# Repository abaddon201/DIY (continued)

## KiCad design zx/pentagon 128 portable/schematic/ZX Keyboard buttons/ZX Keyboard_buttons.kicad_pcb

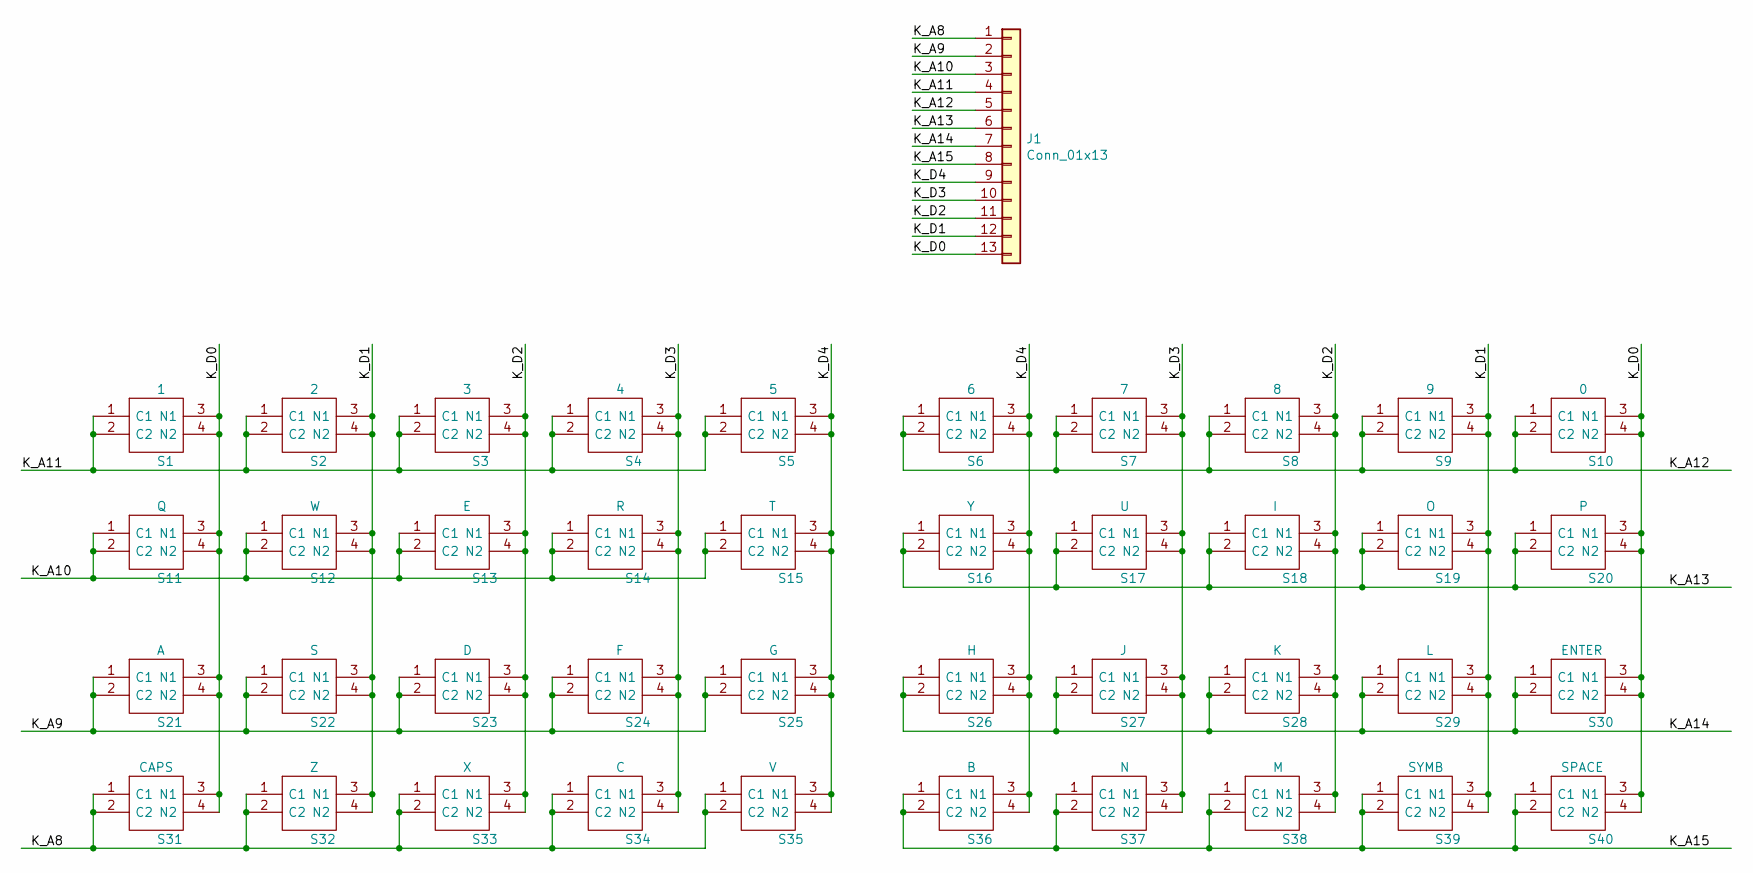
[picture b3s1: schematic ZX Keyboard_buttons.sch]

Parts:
J1: Conn_01x13; PinHeader_1x13_P2.54mm_Vertical
S1: 1; 118259104; Mouser Part Number 506-1-1825910-4
S2: 2; 118259104; Mouser Part Number 506-1-1825910-4
S3: 3; 118259104; Mouser Part Number 506-1-1825910-4
S4: 4; 118259104; Mouser Part Number 506-1-1825910-4
S5: 5; 118259104; Mouser Part Number 506-1-1825910-4
S6: 6; 118259104; Mouser Part Number 506-1-1825910-4
S7: 7; 118259104; Mouser Part Number 506-1-1825910-4
S8: 8; 118259104; Mouser Part Number 506-1-1825910-4
S9: 9; 118259104; Mouser Part Number 506-1-1825910-4
S10: 0; 118259104; Mouser Part Number 506-1-1825910-4
S11: Q; 118259104; Mouser Part Number 506-1-1825910-4
S12: W; 118259104; Mouser Part Number 506-1-1825910-4
S13: E; 118259104; Mouser Part Number 506-1-1825910-4
S14: R; 118259104; Mouser Part Number 506-1-1825910-4
S15: T; 118259104; Mouser Part Number 506-1-1825910-4
S16: Y; 118259104; Mouser Part Number 506-1-1825910-4
S17: U; 118259104; Mouser Part Number 506-1-1825910-4
S18: I; 118259104; Mouser Part Number 506-1-1825910-4
S19: O; 118259104; Mouser Part Number 506-1-1825910-4
S20: P; 118259104; Mouser Part Number 506-1-1825910-4
S21: A; 118259104; Mouser Part Number 506-1-1825910-4
S22: S; 118259104; Mouser Part Number 506-1-1825910-4
S23: D; 118259104; Mouser Part Number 506-1-1825910-4
S24: F; 118259104; Mouser Part Number 506-1-1825910-4
S25: G; 118259104; Mouser Part Number 506-1-1825910-4
S26: H; 118259104; Mouser Part Number 506-1-1825910-4
S27: J; 118259104; Mouser Part Number 506-1-1825910-4
S28: K; 118259104; Mouser Part Number 506-1-1825910-4
S29: L; 118259104; Mouser Part Number 506-1-1825910-4
S30: ENTER; 118259104; Mouser Part Number 506-1-1825910-4
S31: CAPS; 118259104; Mouser Part Number 506-1-1825910-4
S32: Z; 118259104; Mouser Part Number 506-1-1825910-4
S33: X; 118259104; Mouser Part Number 506-1-1825910-4
S34: C; 118259104; Mouser Part Number 506-1-1825910-4
S35: V; 118259104; Mouser Part Number 506-1-1825910-4
S36: B; 118259104; Mouser Part Number 506-1-1825910-4
S37: N; 118259104; Mouser Part Number 506-1-1825910-4
S38: M; 118259104; Mouser Part Number 506-1-1825910-4
S39: SYMB; 118259104; Mouser Part Number 506-1-1825910-4
S40: SPACE; 118259104; Mouser Part Number 506-1-1825910-4

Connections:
/K_A8: J1.1, S31.1 (C1), S31.2 (C2), S32.1 (C1), S32.2 (C2), S33.1 (C1), S33.2 (C2), S34.1 (C1), S34.2 (C2), S35.1 (C1), S35.2 (C2)
/K_A9: J1.2, S21.1 (C1), S21.2 (C2), S22.1 (C1), S22.2 (C2), S23.1 (C1), S23.2 (C2), S24.1 (C1), S24.2 (C2), S25.1 (C1), S25.2 (C2)
/K_A10: J1.3, S11.1 (C1), S11.2 (C2), S12.1 (C1), S12.2 (C2), S13.1 (C1), S13.2 (C2), S14.1 (C1), S14.2 (C2), S15.1 (C1), S15.2 (C2)
/K_A11: J1.4, S1.1 (C1), S1.2 (C2), S2.1 (C1), S2.2 (C2), S3.1 (C1), S3.2 (C2), S4.1 (C1), S4.2 (C2), S5.1 (C1), S5.2 (C2)
/K_A12: J1.5, S6.1 (C1), S6.2 (C2), S7.1 (C1), S7.2 (C2), S8.1 (C1), S8.2 (C2), S9.1 (C1), S9.2 (C2), S10.1 (C1), S10.2 (C2)
/K_A13: J1.6, S16.1 (C1), S16.2 (C2), S17.1 (C1), S17.2 (C2), S18.1 (C1), S18.2 (C2), S19.1 (C1), S19.2 (C2), S20.1 (C1), S20.2 (C2)
/K_A14: J1.7, S26.1 (C1), S26.2 (C2), S27.1 (C1), S27.2 (C2), S28.1 (C1), S28.2 (C2), S29.1 (C1), S29.2 (C2), S30.1 (C1), S30.2 (C2)
/K_A15: J1.8, S36.1 (C1), S36.2 (C2), S37.1 (C1), S37.2 (C2), S38.1 (C1), S38.2 (C2), S39.1 (C1), S39.2 (C2), S40.1 (C1), S40.2 (C2)
/K_D0: J1.13, S1.3 (N1), S1.4 (N2), S10.3 (N1), S10.4 (N2), S11.3 (N1), S11.4 (N2), S20.3 (N1), S20.4 (N2), S21.3 (N1), S21.4 (N2), S30.3 (N1), S30.4 (N2), S31.3 (N1), S31.4 (N2), S40.3 (N1), S40.4 (N2)
/K_D1: J1.12, S2.3 (N1), S2.4 (N2), S9.3 (N1), S9.4 (N2), S12.3 (N1), S12.4 (N2), S19.3 (N1), S19.4 (N2), S22.3 (N1), S22.4 (N2), S29.3 (N1), S29.4 (N2), S32.3 (N1), S32.4 (N2), S39.3 (N1), S39.4 (N2)
/K_D2: J1.11, S3.3 (N1), S3.4 (N2), S8.3 (N1), S8.4 (N2), S13.3 (N1), S13.4 (N2), S18.3 (N1), S18.4 (N2), S23.3 (N1), S23.4 (N2), S28.3 (N1), S28.4 (N2), S33.3 (N1), S33.4 (N2), S38.3 (N1), S38.4 (N2)
/K_D3: J1.10, S4.3 (N1), S4.4 (N2), S7.3 (N1), S7.4 (N2), S14.3 (N1), S14.4 (N2), S17.3 (N1), S17.4 (N2), S24.3 (N1), S24.4 (N2), S27.3 (N1), S27.4 (N2), S34.3 (N1), S34.4 (N2), S37.3 (N1), S37.4 (N2)
/K_D4: J1.9, S5.3 (N1), S5.4 (N2), S6.3 (N1), S6.4 (N2), S15.3 (N1), S15.4 (N2), S16.3 (N1), S16.4 (N2), S25.3 (N1), S25.4 (N2), S26.3 (N1), S26.4 (N2), S35.3 (N1), S35.4 (N2), S36.3 (N1), S36.4 (N2)

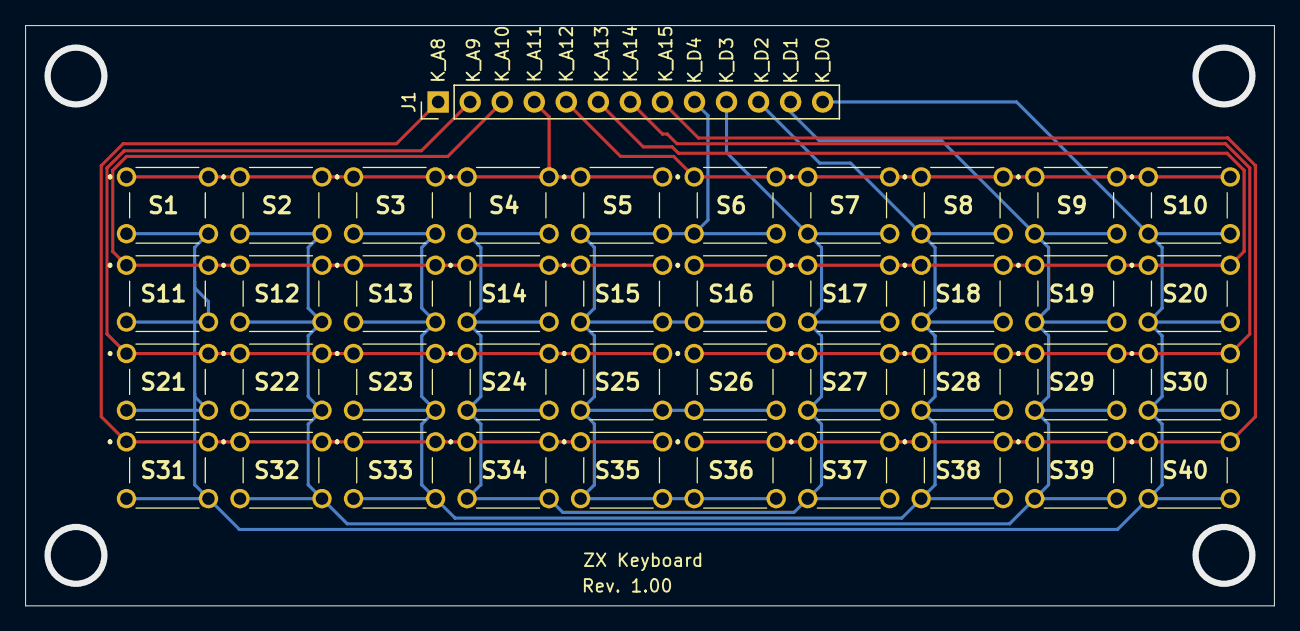
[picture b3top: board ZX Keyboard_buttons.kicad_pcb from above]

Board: 2 copper layers, 99.0 x 46.0 mm, 41 parts (0 on the bottom side), 13 nets.

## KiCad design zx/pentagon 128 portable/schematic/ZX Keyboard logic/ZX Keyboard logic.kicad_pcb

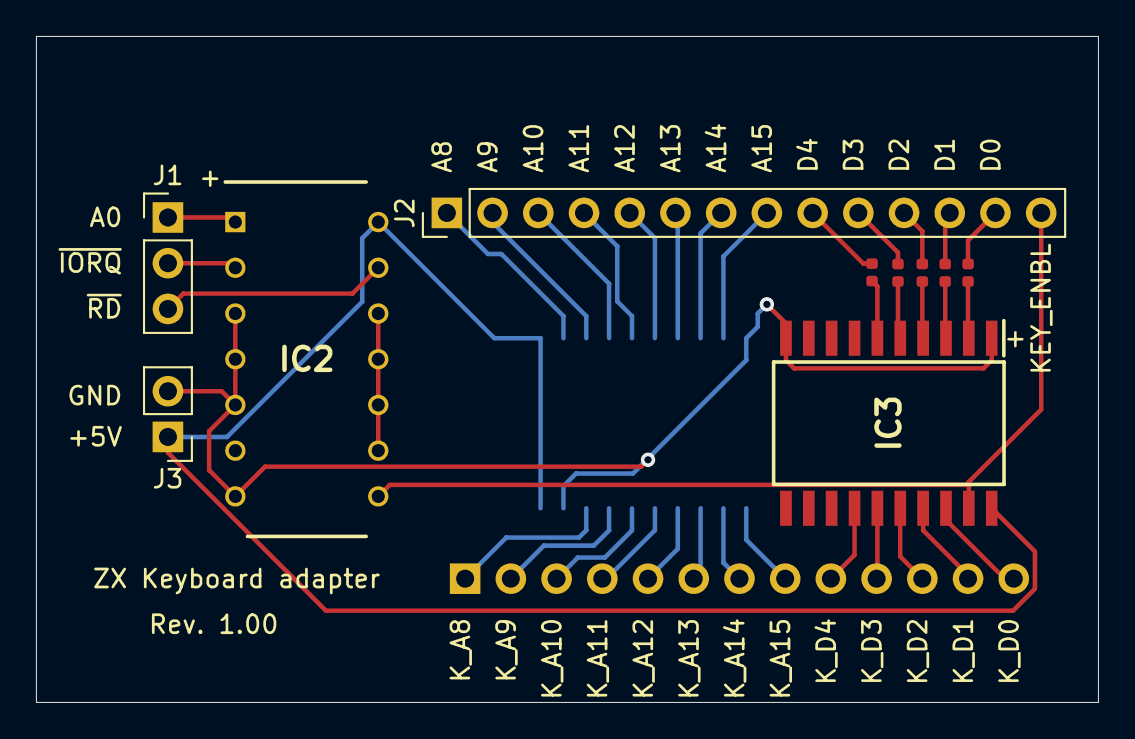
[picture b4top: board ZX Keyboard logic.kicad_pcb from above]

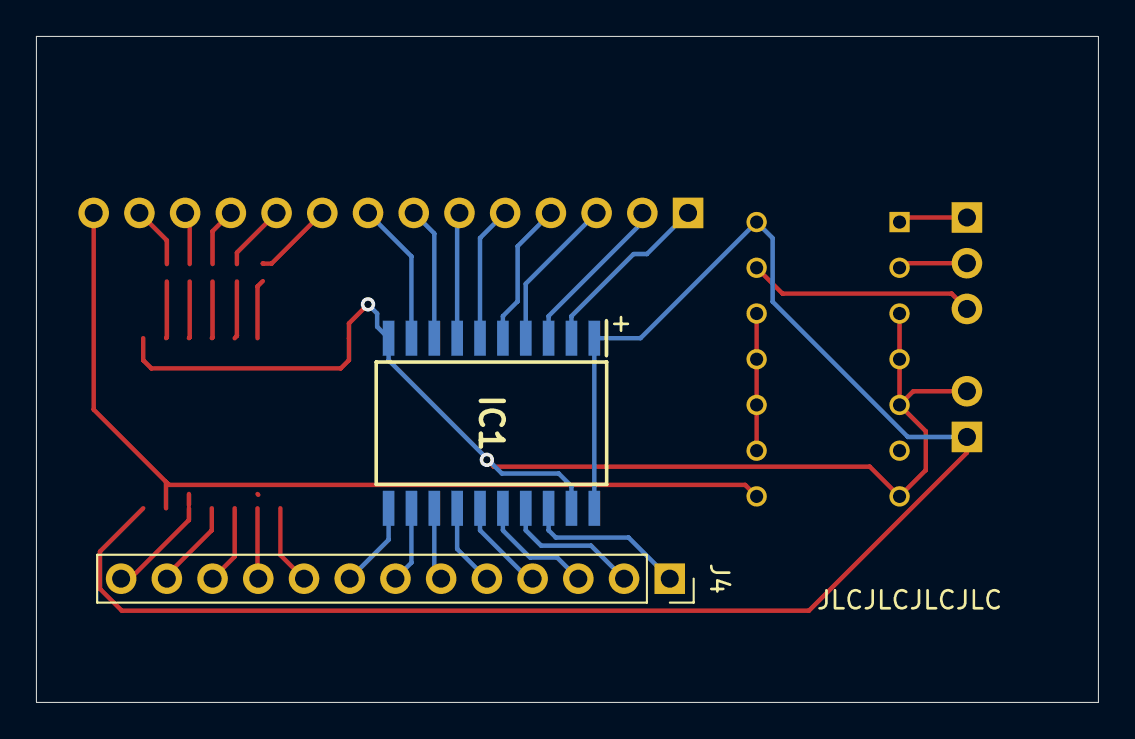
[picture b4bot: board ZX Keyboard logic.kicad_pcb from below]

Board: 2 copper layers, 59.0 x 37.0 mm, 12 parts (2 on the bottom side), 38 nets.

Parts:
IC1, IC3: SN74LS245DW; SOIC127P1030X265-20N
IC2: SN74LS27N; DIP794W53P254L1930H508Q14N
J1: Conn_01x03; PinHeader_1x03_P2.54mm_Vertical
J2: Conn_01x14; PinHeader_1x14_P2.54mm_Vertical
J3: Conn_01x02; PinHeader_1x02_P2.54mm_Vertical
J4: Conn_01x13; PinSocket_1x13_P2.54mm_Vertical
R1, R2, R3, R4: 1.5K; R_0402_1005Metric
R?-R1: 1.5K; R_0402_1005Metric

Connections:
+5V: IC1.1, IC1.20, IC2.14, IC3.20, J3.1
/A0: IC2.1, J1.1
/A8: IC1.2, J2.1
/A9: IC1.3, J2.2
/A10: IC1.4, J2.3
/A11: IC1.5, J2.4
/A12: IC1.6, J2.5
/A13: IC1.7, J2.6
/A14: IC1.8, J2.7
/A15: IC1.9, J2.8
/D0: J2.13, R?-R1.2
/D1: J2.12, R1.2
/D2: J2.11, R2.2
/D3: J2.10, R3.2
/D4: J2.9, R4.2
/KEY_ENBL: IC2.8, IC3.19, J2.14
/K_A8: IC1.18, J4.1
/K_A9: IC1.17, J4.2
/K_A10: IC1.16, J4.3
/K_A11: IC1.15, J4.4
/K_A12: IC1.14, J4.5
/K_A13: IC1.13, J4.6
/K_A14: IC1.12, J4.7
/K_A15: IC1.11, J4.8
/K_D0: IC3.18, J4.13
/K_D1: IC3.17, J4.12
/K_D2: IC3.16, J4.11
/K_D3: IC3.15, J4.10
/K_D4: IC3.14, J4.9
/~IORQ: IC2.2, J1.2
/~RD: IC2.13, J1.3
GND: IC1.10, IC1.19, IC2.3, IC2.4, IC2.5, IC2.7, IC3.1, IC3.10, J3.2
unnamed: IC2.9, IC2.10, IC2.11, IC2.12
unnamed: IC3.2, R?-R1.1
unnamed: IC3.3, R1.1
unnamed: IC3.4, R2.1
unnamed: IC3.5, R3.1
unnamed: IC3.6, R4.1

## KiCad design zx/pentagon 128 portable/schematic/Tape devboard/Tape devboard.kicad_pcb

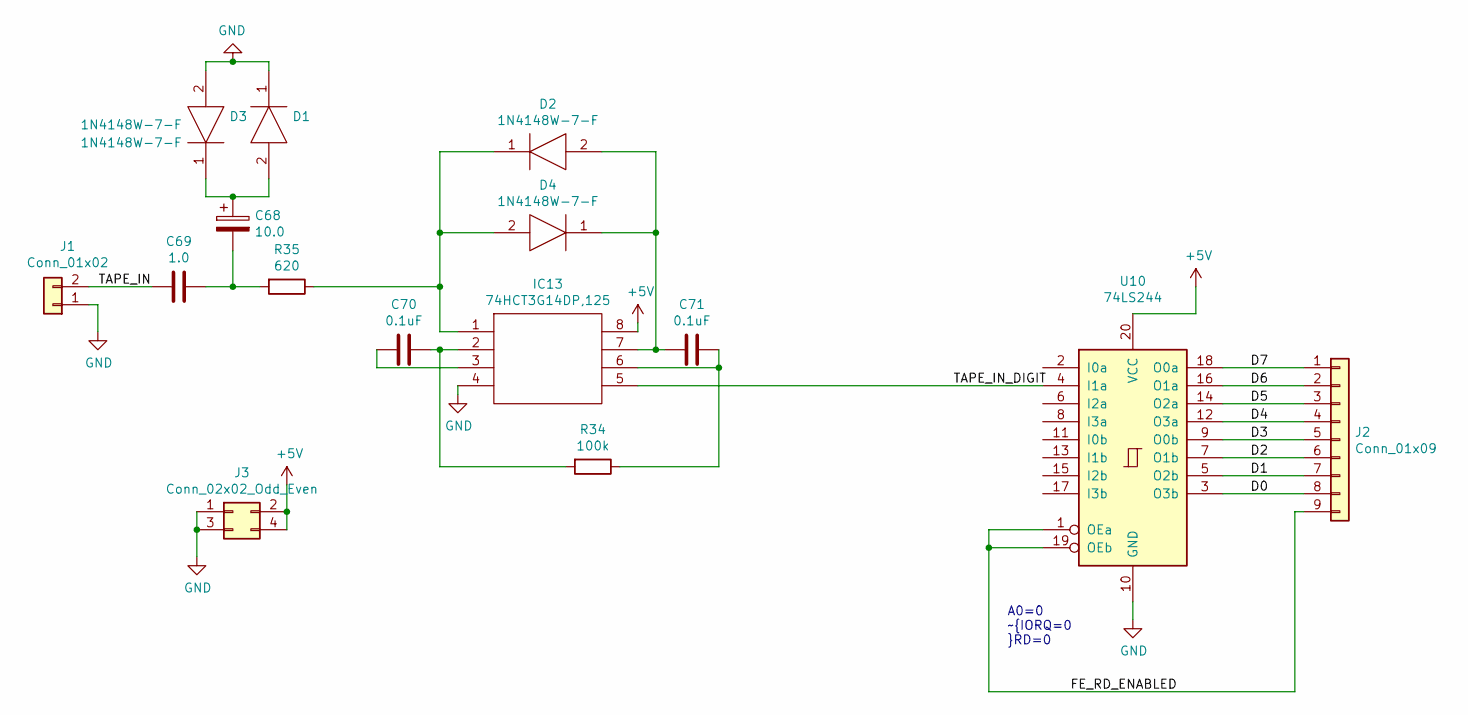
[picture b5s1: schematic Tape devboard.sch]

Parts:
C68: 10.0; C_0402_1005Metric
C69: 1.0; C_0402_1005Metric
C70, C71: 0.1uF; C_0402_1005Metric
D1, D2, D3, D4: 1N4148W-7-F; SOD3716X145N; Mouser Part Number 621-1N4148W-F
IC13: 74HCT3G14DP,125; SOP65P400X110-8N; Mouser Part Number 771-HCT3G14DP125
J1: Conn_01x02; PinHeader_1x02_P2.54mm_Vertical
J2: Conn_01x09; PinHeader_1x09_P2.54mm_Vertical
J3: Conn_02x02_Odd_Even; PinHeader_2x02_P2.54mm_Vertical
R34: 100k; R_0402_1005Metric
R35: 620; R_0402_1005Metric
U10: 74LS244; SSOP-20_5.3x7.2mm_P0.65mm; Mouser Part Number 595-SN74LS244DBR

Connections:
+5V: IC13.8, J3.2, J3.4, U10.20 (VCC)
/D0: J2.8, U10.3 (O3b)
/D1: J2.7, U10.5 (O2b)
/D2: J2.6, U10.7 (O1b)
/D3: J2.5, U10.9 (O0b)
/D4: J2.4, U10.12 (O3a)
/D5: J2.3, U10.14 (O2a)
/D6: J2.2, U10.16 (O1a)
/D7: J2.1, U10.18 (O0a)
/FE_RD_ENABLED: J2.9, U10.1 (OEa), U10.19 (OEb)
/TAPE_IN: C69.2, J1.2
/TAPE_IN_DIGIT: IC13.5, U10.4 (I1a)
GND: D1.1, D3.2, IC13.4, J1.1, J3.1, J3.3, U10.10 (GND)
unnamed: C68.1, D1.2, D3.1
unnamed: C68.2, C69.1, R35.2
unnamed: C70.1, IC13.2, R34.2
unnamed: C70.2, IC13.3
unnamed: C71.1, IC13.6, R34.1
unnamed: C71.2, D2.2, D4.1, IC13.7
unnamed: D2.1, D4.2, IC13.1, R35.1

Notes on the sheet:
A0=0 ~IORQ=0 ~RD=0

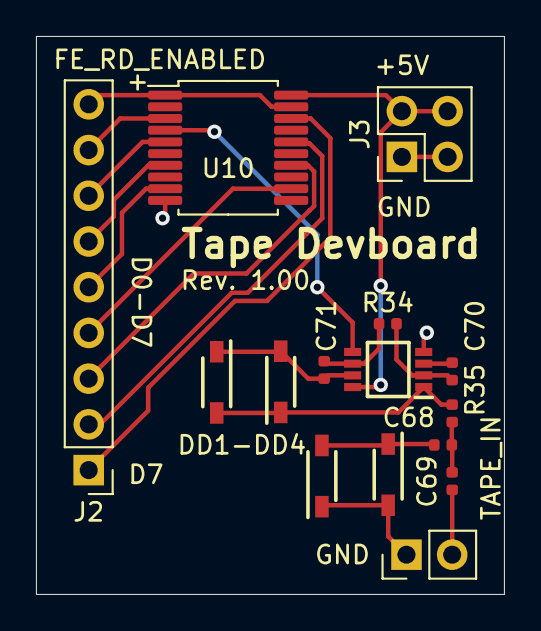
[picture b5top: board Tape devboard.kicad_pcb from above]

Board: 2 copper layers, 26.0 x 31.0 mm, 15 parts (0 on the bottom side), 20 nets.

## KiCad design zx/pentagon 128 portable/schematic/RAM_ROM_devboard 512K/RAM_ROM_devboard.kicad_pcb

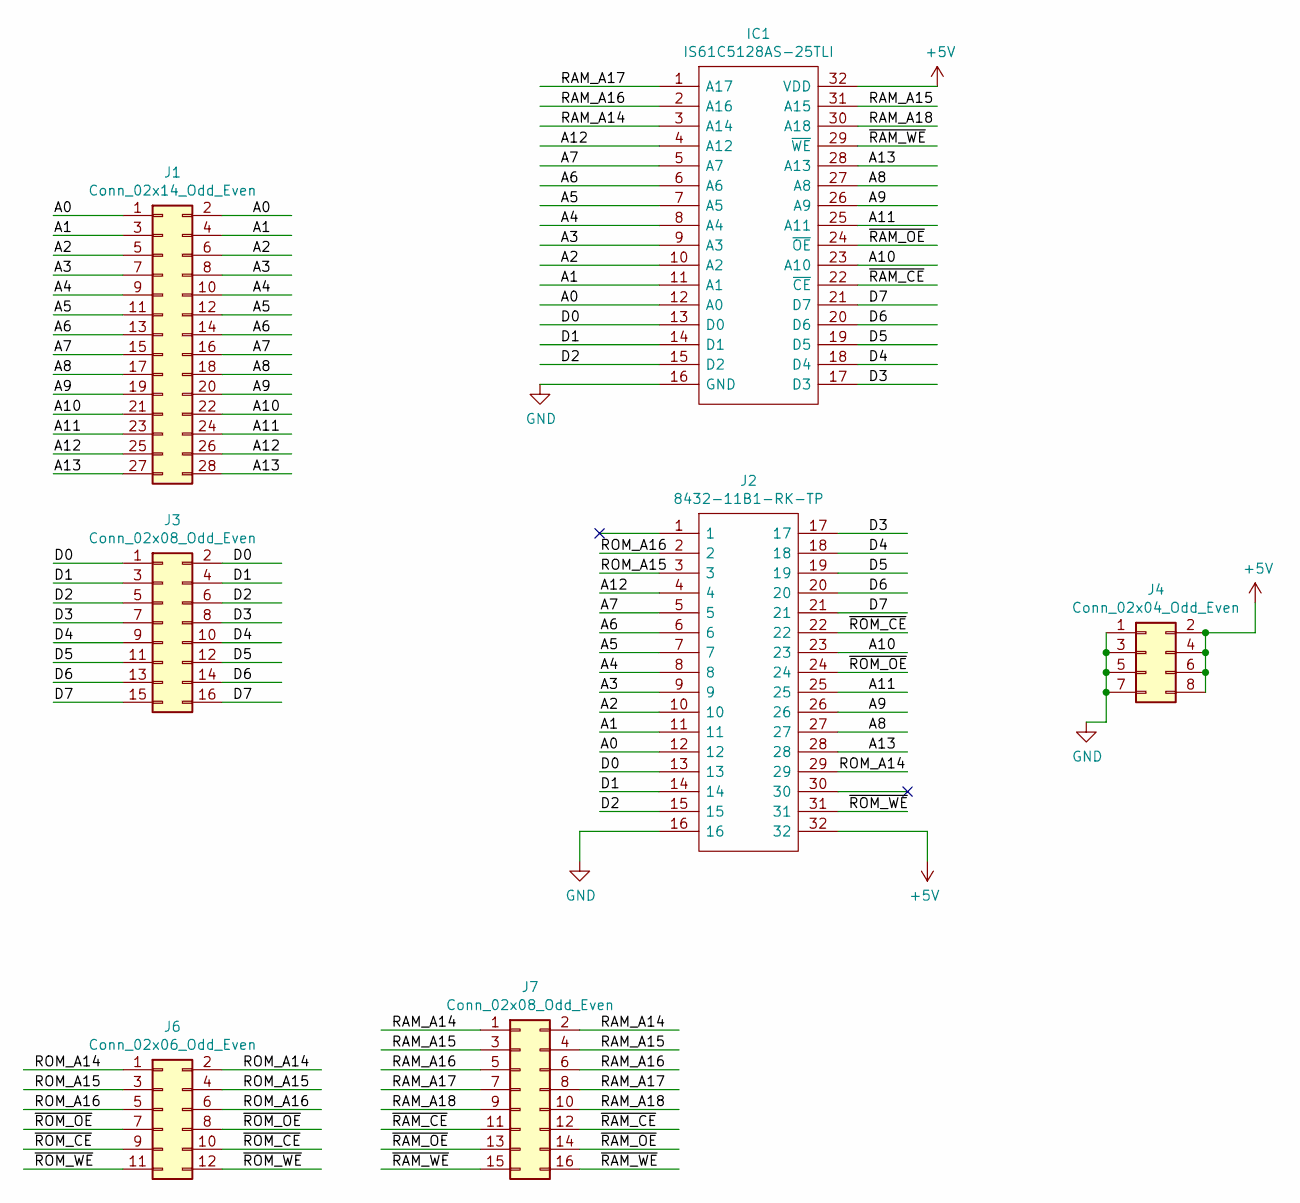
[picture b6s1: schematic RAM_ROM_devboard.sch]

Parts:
IC1: IS61C5128AS-25TLI; SOIC127P1176X120-32N; Mouser Part Number 870-61C5128AS-25TLI
J1: Conn_02x14_Odd_Even; PinHeader_2x14_P2.54mm_Vertical
J2: 8432-11B1-RK-TP; 843211B1RKTP; Mouser Part Number 517-8432-11B1-RK-TP
J3, J7: Conn_02x08_Odd_Even; PinHeader_2x08_P2.54mm_Vertical
J4: Conn_02x04_Odd_Even; PinHeader_2x04_P2.54mm_Vertical
J6: Conn_02x06_Odd_Even; PinHeader_2x06_P2.54mm_Vertical

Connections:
+5V: IC1.32 (VDD), J2.32, J4.2, J4.4, J4.6, J4.8
/A0: IC1.12 (A0), J1.1, J1.2, J2.12
/A1: IC1.11 (A1), J1.3, J1.4, J2.11
/A2: IC1.10 (A2), J1.5, J1.6, J2.10
/A3: IC1.9 (A3), J1.7, J1.8, J2.9
/A4: IC1.8 (A4), J1.9, J1.10, J2.8
/A5: IC1.7 (A5), J1.11, J1.12, J2.7
/A6: IC1.6 (A6), J1.13, J1.14, J2.6
/A7: IC1.5 (A7), J1.15, J1.16, J2.5
/A8: IC1.27 (A8), J1.17, J1.18, J2.27
/A9: IC1.26 (A9), J1.19, J1.20, J2.26
/A10: IC1.23 (A10), J1.21, J1.22, J2.23
/A11: IC1.25 (A11), J1.23, J1.24, J2.25
/A12: IC1.4 (A12), J1.25, J1.26, J2.4
/A13: IC1.28 (A13), J1.27, J1.28, J2.28
/D0: IC1.13 (D0), J2.13, J3.1, J3.2
/D1: IC1.14 (D1), J2.14, J3.3, J3.4
/D2: IC1.15 (D2), J2.15, J3.5, J3.6
/D3: IC1.17 (D3), J2.17, J3.7, J3.8
/D4: IC1.18 (D4), J2.18, J3.9, J3.10
/D5: IC1.19 (D5), J2.19, J3.11, J3.12
/D6: IC1.20 (D6), J2.20, J3.13, J3.14
/D7: IC1.21 (D7), J2.21, J3.15, J3.16
/RAM_A14: IC1.3 (A14), J7.1, J7.2
/RAM_A15: IC1.31 (A15), J7.3, J7.4
/RAM_A16: IC1.2 (A16), J7.5, J7.6
/RAM_A17: IC1.1 (A17), J7.7, J7.8
/RAM_A18: IC1.30 (A18), J7.9, J7.10
/ROM_A14: J2.29, J6.1, J6.2
/ROM_A15: J2.3, J6.3, J6.4
/ROM_A16: J2.2, J6.5, J6.6
/~RAM_CE: IC1.22 (~CE), J7.11, J7.12
/~RAM_OE: IC1.24 (~OE), J7.13, J7.14
/~RAM_WE: IC1.29 (~WE), J7.15, J7.16
/~ROM_CE: J2.22, J6.9, J6.10
/~ROM_OE: J2.24, J6.7, J6.8
/~ROM_WE: J2.31, J6.11, J6.12
GND: IC1.16 (GND), J2.16, J4.1, J4.3, J4.5, J4.7

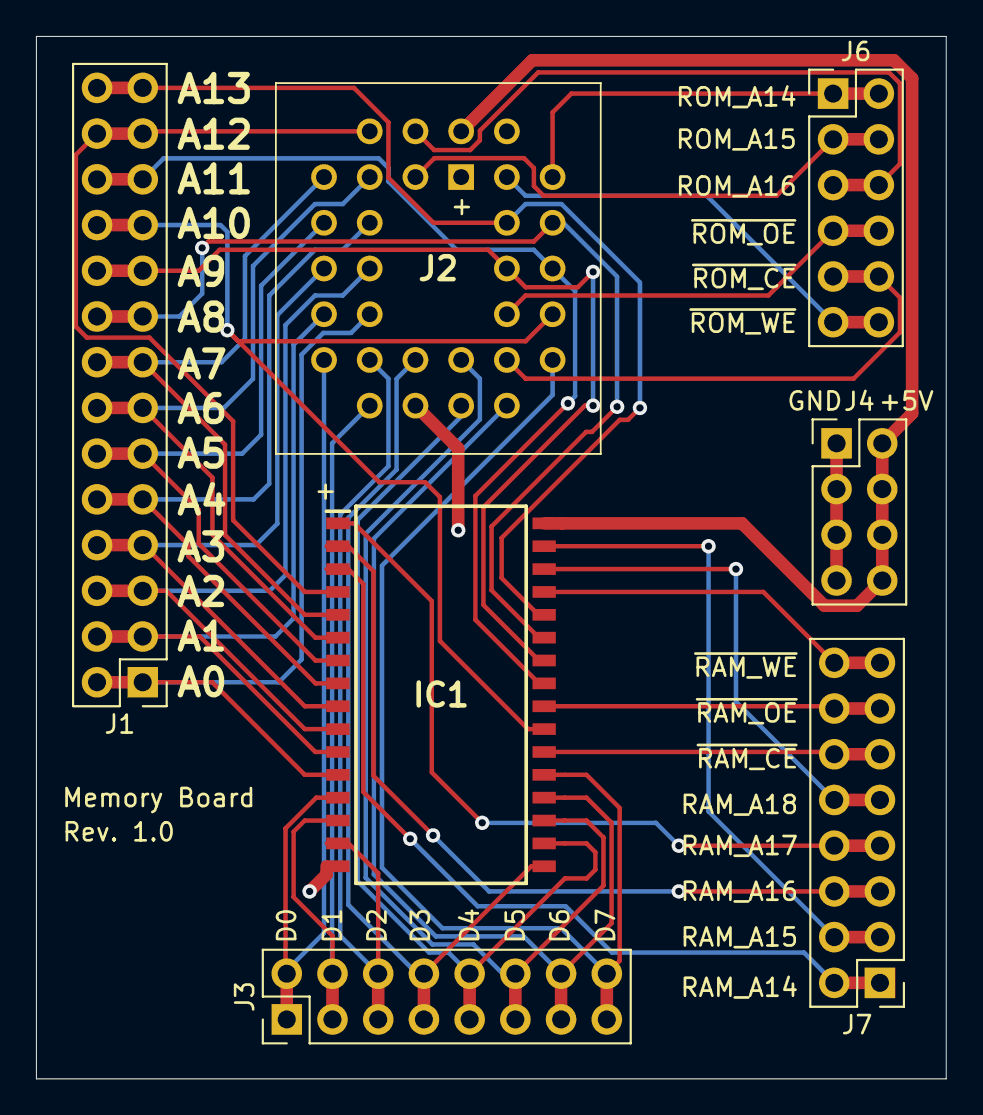
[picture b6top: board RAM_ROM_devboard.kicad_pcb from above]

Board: 2 copper layers, 50.5 x 57.9 mm, 7 parts (0 on the bottom side), 38 nets.

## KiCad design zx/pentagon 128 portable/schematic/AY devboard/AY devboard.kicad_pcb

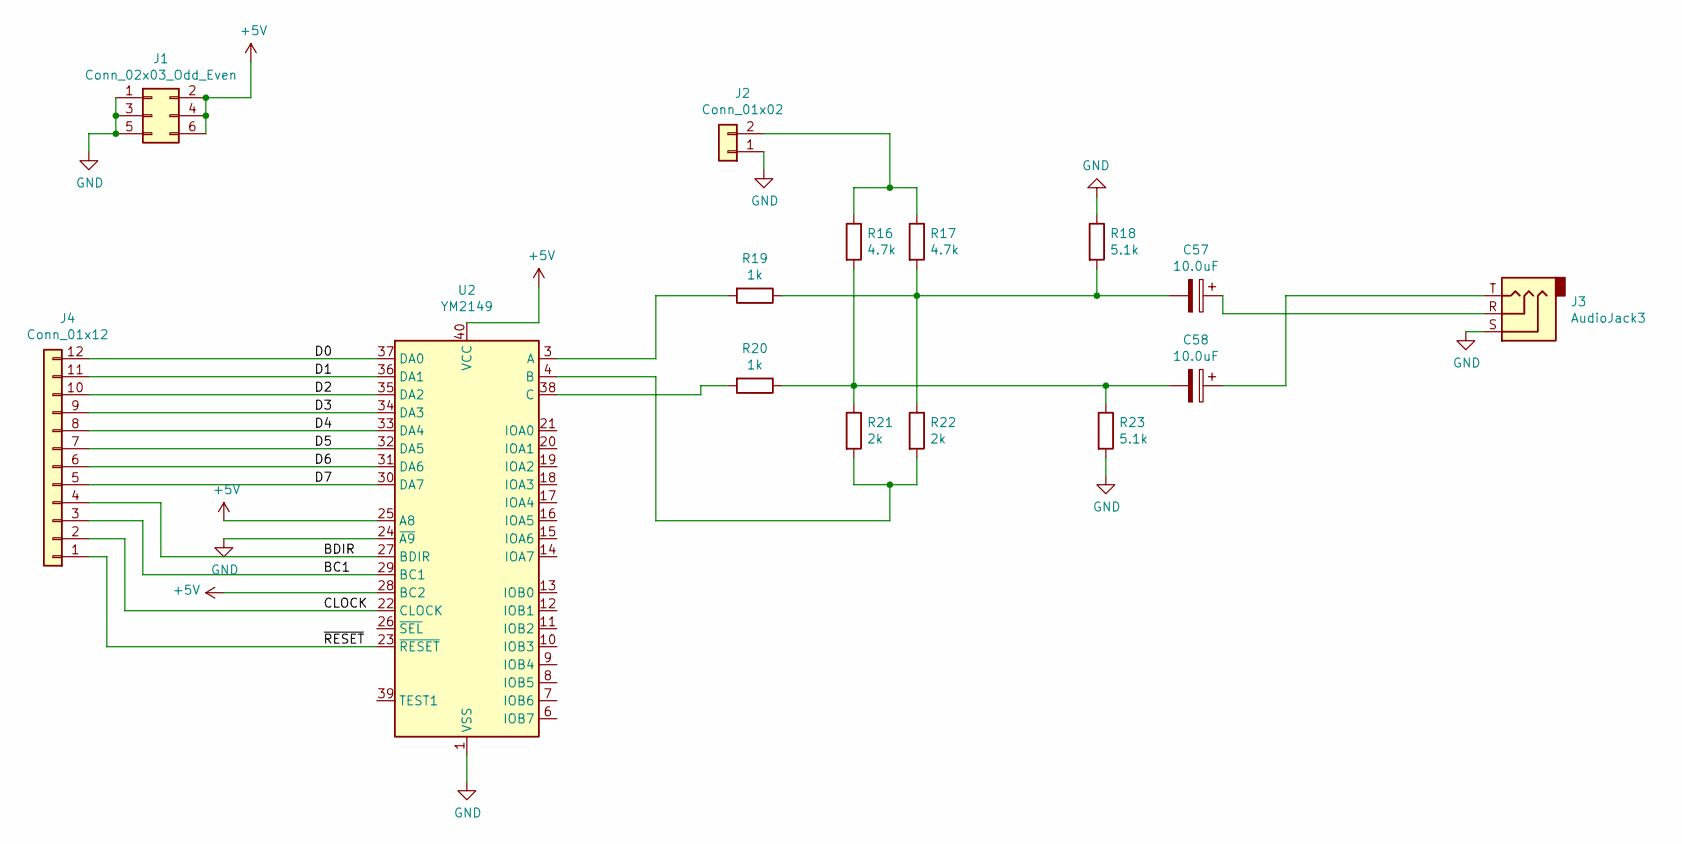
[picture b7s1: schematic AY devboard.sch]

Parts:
C57, C58: 10.0uF; C_0402_1005Metric
J1: Conn_02x03_Odd_Even; PinHeader_2x03_P2.54mm_Vertical
J2: Conn_01x02; PinHeader_1x02_P2.54mm_Vertical
J3: AudioJack3; Jack_3.5mm_CUI_SJ1-3533NG_Horizontal_CircularHoles
J4: Conn_01x12; PinHeader_1x12_P2.54mm_Vertical
R16, R17: 4.7k; R_0402_1005Metric
R18, R23: 5.1k; R_0402_1005Metric
R19, R20: 1k; R_0402_1005Metric
R21, R22: 2k; R_0402_1005Metric
U2: YM2149; DIP-40_W15.24mm

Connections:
+5V: J1.2, J1.4, J1.6, U2.25 (A8), U2.28 (BC2), U2.40 (VCC)
/BC1: J4.3, U2.29 (BC1)
/BDIR: J4.4, U2.27 (BDIR)
/CLOCK: J4.2, U2.22 (CLOCK)
/D0: J4.12, U2.37 (DA0)
/D1: J4.11, U2.36 (DA1)
/D2: J4.10, U2.35 (DA2)
/D3: J4.9, U2.34 (DA3)
/D4: J4.8, U2.33 (DA4)
/D5: J4.7, U2.32 (DA5)
/D6: J4.6, U2.31 (DA6)
/D7: J4.5, U2.30 (DA7)
/~RESET: J4.1, U2.23 (~RESET)
GND: J1.1, J1.3, J1.5, J2.1, J3.S, R18.1, R23.2, U2.1 (VSS), U2.24 (~A9)
unnamed: C57.1, J3.R
unnamed: C57.2, R17.2, R18.2, R19.1, R22.1
unnamed: C58.1, J3.T
unnamed: C58.2, R16.2, R20.1, R21.1, R23.1
unnamed: J2.2, R16.1, R17.1
unnamed: R19.2, U2.3 (A)
unnamed: R20.2, U2.38 (C)
unnamed: R21.2, R22.2, U2.4 (B)

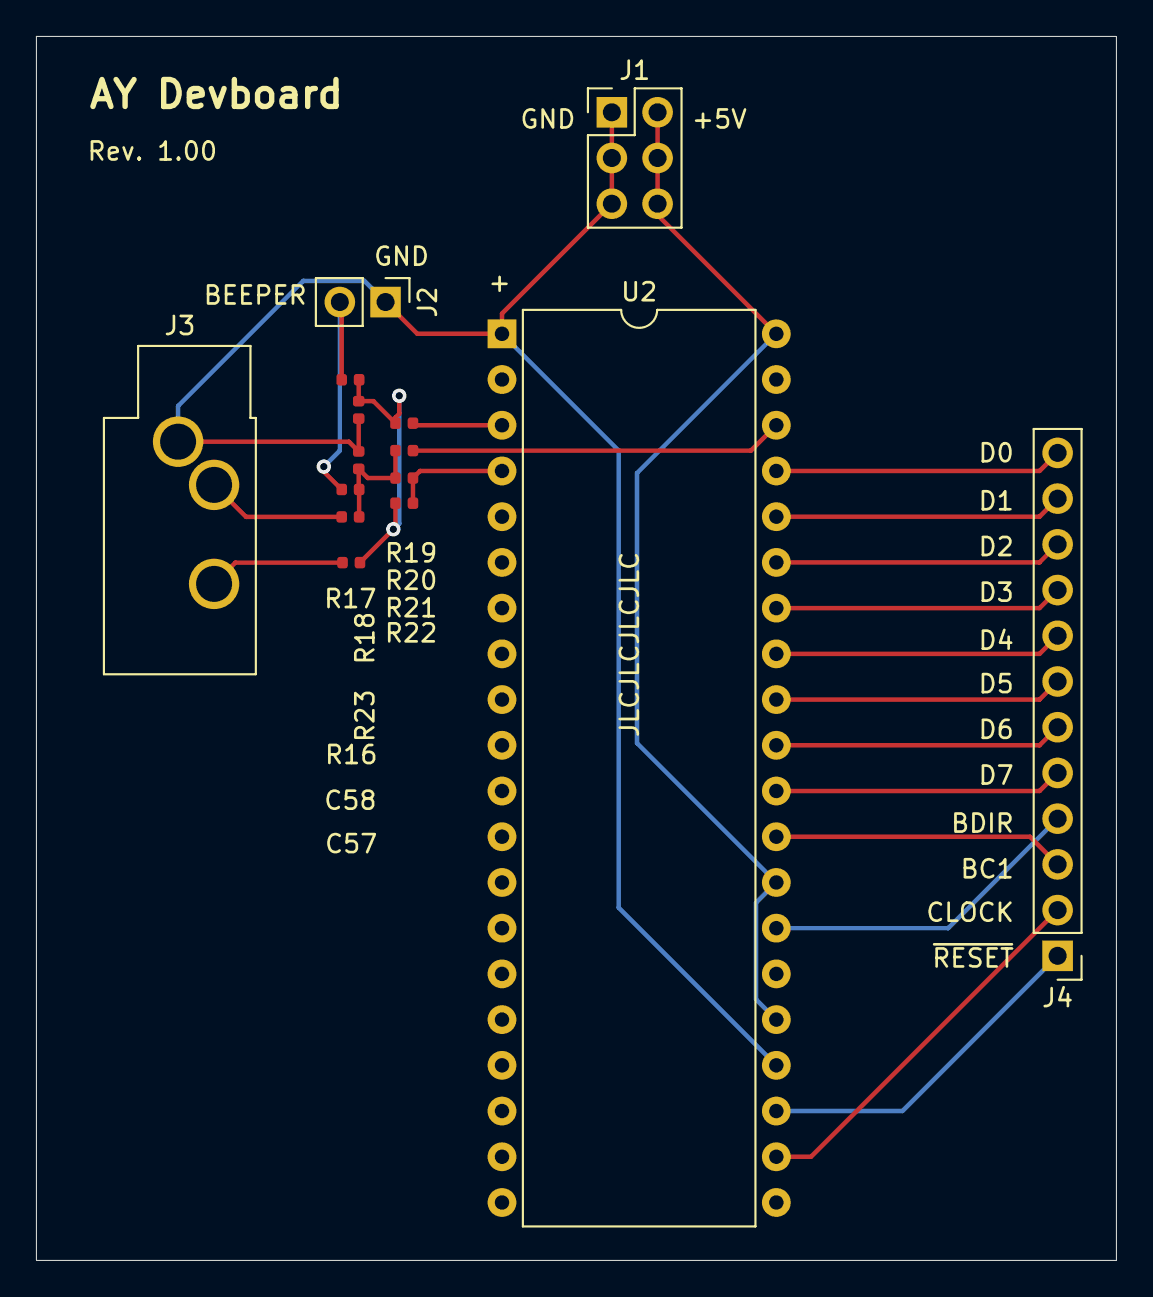
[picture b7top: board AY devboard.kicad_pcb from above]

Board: 2 copper layers, 60.0 x 68.0 mm, 15 parts (0 on the bottom side), 22 nets.

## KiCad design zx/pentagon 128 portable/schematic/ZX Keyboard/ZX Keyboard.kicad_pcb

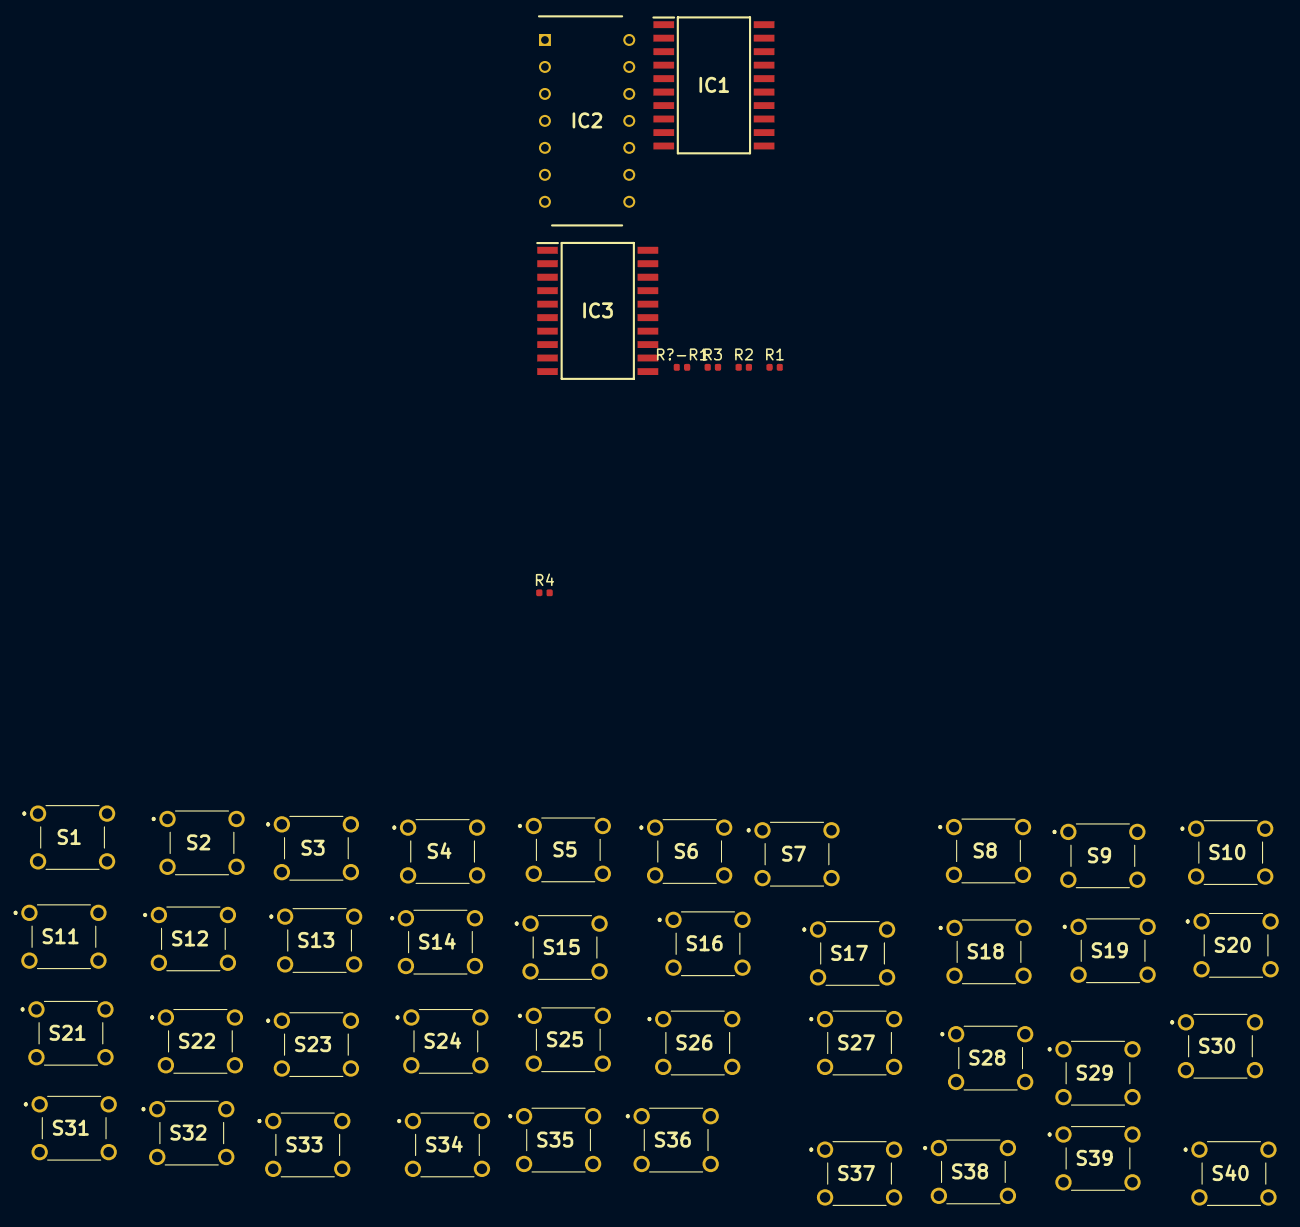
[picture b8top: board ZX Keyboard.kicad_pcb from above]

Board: 2 copper layers, 48 parts (0 on the bottom side), 22 nets, no tracks yet.

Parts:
IC1, IC3: SN74LS245DW; SOIC127P1030X265-20N
IC2: SN74LS27N; DIP794W53P254L1930H508Q14N
R1, R2, R3, R4: 1.5K; R_0402_1005Metric
R?-R1: 1.5K; R_0402_1005Metric
S1: 1; 118259104
S2: 2; 118259104
S3: 3; 118259104
S4: 4; 118259104
S5: 5; 118259104
S6: 6; 118259104
S7: 7; 118259104
S8: 8; 118259104
S9: 9; 118259104
S10: 0; 118259104
S11: Q; 118259104
S12: W; 118259104
S13: E; 118259104
S14: R; 118259104
S15: T; 118259104
S16: Y; 118259104
S17: U; 118259104
S18: I; 118259104
S19: O; 118259104
S20: P; 118259104
S21: A; 118259104
S22: S; 118259104
S23: D; 118259104
S24: F; 118259104
S25: G; 118259104
S26: H; 118259104
S27: J; 118259104
S28: K; 118259104
S29: L; 118259104
S30: ENTER; 118259104
S31: CAPS; 118259104
S32: Z; 118259104
S33: X; 118259104
S34: C; 118259104
S35: V; 118259104
S36: B; 118259104
S37: N; 118259104
S38: M; 118259104
S39: SYMB; 118259104
S40: SPACE; 118259104

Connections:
+5V: IC1.1, IC1.20, IC2.14, IC3.20
/KEY_ENBL: IC2.8, IC3.19
/K_A8: IC1.18, S31.1, S31.2, S32.1, S32.2, S33.1, S33.2, S34.1, S34.2, S35.1, S35.2
/K_A9: IC1.17, S21.1, S21.2, S22.1, S22.2, S23.1, S23.2, S24.1, S24.2, S25.1, S25.2
/K_A10: IC1.16, S11.1, S11.2, S12.1, S12.2, S13.1, S13.2, S14.1, S14.2, S15.1, S15.2
/K_A11: IC1.15, S1.1, S1.2, S2.1, S2.2, S3.1, S3.2, S4.1, S4.2, S5.1, S5.2
/K_A12: IC1.14, S6.1, S6.2, S7.1, S7.2, S8.1, S8.2, S9.1, S9.2, S10.1, S10.2
/K_A13: IC1.13, S16.1, S16.2, S17.1, S17.2, S18.1, S18.2, S19.1, S19.2, S20.1, S20.2
/K_A14: IC1.12, S26.1, S26.2, S27.1, S27.2, S28.1, S28.2, S29.1, S29.2, S30.1, S30.2
/K_A15: IC1.11, S36.1, S36.2, S37.1, S37.2, S38.1, S38.2, S39.1, S39.2, S40.1, S40.2
/K_D0: IC3.18, S1.3, S1.4, S10.3, S10.4, S11.3, S11.4, S20.3, S20.4, S21.3, S21.4, S30.3, S30.4, S31.3, S31.4, S40.3, S40.4
/K_D1: IC3.17, S2.3, S2.4, S9.3, S9.4, S12.3, S12.4, S19.3, S19.4, S22.3, S22.4, S29.3, S29.4, S32.3, S32.4, S39.3, S39.4
/K_D2: IC3.16, S3.3, S3.4, S8.3, S8.4, S13.3, S13.4, S18.3, S18.4, S23.3, S23.4, S28.3, S28.4, S33.3, S33.4, S38.3, S38.4
/K_D3: IC3.15, S4.3, S4.4, S7.3, S7.4, S14.3, S14.4, S17.3, S17.4, S24.3, S24.4, S27.3, S27.4, S34.3, S34.4, S37.3, S37.4
/K_D4: IC3.14, S5.3, S5.4, S6.3, S6.4, S15.3, S15.4, S16.3, S16.4, S25.3, S25.4, S26.3, S26.4, S35.3, S35.4, S36.3, S36.4
GND: IC1.10, IC1.19, IC2.7, IC3.1, IC3.10
unnamed: IC2.9, IC2.10, IC2.11, IC2.12
unnamed: IC3.2, R?-R1.1
unnamed: IC3.3, R1.1
unnamed: IC3.4, R2.1
unnamed: IC3.5, R3.1
unnamed: IC3.6, R4.1

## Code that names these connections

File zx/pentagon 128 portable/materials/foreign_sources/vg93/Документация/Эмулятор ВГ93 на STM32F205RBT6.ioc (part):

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Mcu.Name=STM32F205R(B-C-E-F-G)Tx
Mcu.Package=LQFP64
Mcu.UserName=STM32F205RBTx
PA0-WKUP.Signal=GPIO_Input
PA1.Signal=GPIO_Input
PA10.Mode=Asynchronous
PA10.Signal=USART1_RX
PA13.Mode=JTAG_4_pins
PA13.Signal=SYS_JTMS-SWDIO
PA14.Mode=JTAG_4_pins
PA14.Signal=SYS_JTCK-SWCLK
PA15.Mode=JTAG_4_pins
PA15.Signal=SYS_JTDI
PA2.Signal=GPIO_Input
PA3.Signal=GPIO_Input
PA4.Signal=GPIO_Input
PA5.Signal=GPIO_Input
PA6.Signal=GPIO_Input
PA7.Signal=GPIO_Input
PA9.Mode=Asynchronous
PA9.Signal=USART1_TX
PB0.Signal=GPIO_Input
PB1.Signal=GPIO_Input
PB10.Signal=GPIO_Input
PB13.Signal=GPIO_Input
PB14.Signal=GPIO_Input
PB15.Signal=GPIO_Input
PB2.Signal=GPIO_Input
PB3.Mode=JTAG_4_pins
PB3.Signal=SYS_JTDO-SWO
PB5.Signal=GPIO_Input
PB6.Signal=GPIO_Output
PB7.Signal=GPIO_Output
PB8.Mode=I2C
PB8.Signal=I2C1_SCL
PB9.Mode=I2C
PB9.Signal=I2C1_SDA
PC10.Mode=SD_4_bits_Wide_bus
PC10.Signal=SDIO_D2
PC11.Mode=SD_4_bits_Wide_bus
PC11.Signal=SDIO_D3
PC12.Mode=SD_4_bits_Wide_bus
PC12.Signal=SDIO_CK
PC13.Signal=GPIO_Input
PC5.Signal=GPIO_Input
PC6.Signal=GPIO_Input
PC8.Mode=SD_4_bits_Wide_bus
PC8.Signal=SDIO_D0
PC9.Mode=SD_4_bits_Wide_bus
PC9.Signal=SDIO_D1
PD2.Mode=SD_4_bits_Wide_bus
PD2.Signal=SDIO_CMD
PH0-OSC_IN.Mode=HSE-External-Oscillator
PH0-OSC_IN.Signal=RCC_OSC_IN
PH1-OSC_OUT.Mode=HSE-External-Oscillator
PH1-OSC_OUT.Signal=RCC_OSC_OUT
RCC.HSE_VALUE=25000000
RCC.SYSCLKFreq_VALUE=120000000
RCC.SYSCLKSource=RCC_SYSCLKSOURCE_PLLCLK

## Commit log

2016-05-11 moved to english named folder
2016-05-11 removed speaker, added AOUT pin, added power connector pins
2016-05-12 added + sign for DC connector
2020-09-09 added zx
2020-09-10 updated power lines
2020-09-11 upadted connectors
2020-09-12 update devboard routing
2020-09-15 added memory devboard, moved devboard to schematic
2020-09-15 updated board and notes
2020-09-15 updated docs
2020-09-16 updated focs, added Z80 devboard
2020-09-17 added ZX Keyboard
2020-09-17 reorganized folders
2020-09-18 reorganizing. finished ram and keyboard, updated z80
2020-09-18 repo reoganise
2020-09-18 fixed keyboard
2020-09-18 updated ram 128k, 512k, keyboard
2020-09-18 some reordering in the main project
2020-09-18 updated schemes
2020-09-19 added AY devboard
2020-09-19 added tape in devboard
2020-09-19 updated BOM
2020-09-19 bom updates
2020-09-19 tap2wav
2020-09-22 added z80 pdip. updated all boards
2020-10-12 fixed 496 devboard
    fixed tracks for oscillators
2022-03-04 pentagon
